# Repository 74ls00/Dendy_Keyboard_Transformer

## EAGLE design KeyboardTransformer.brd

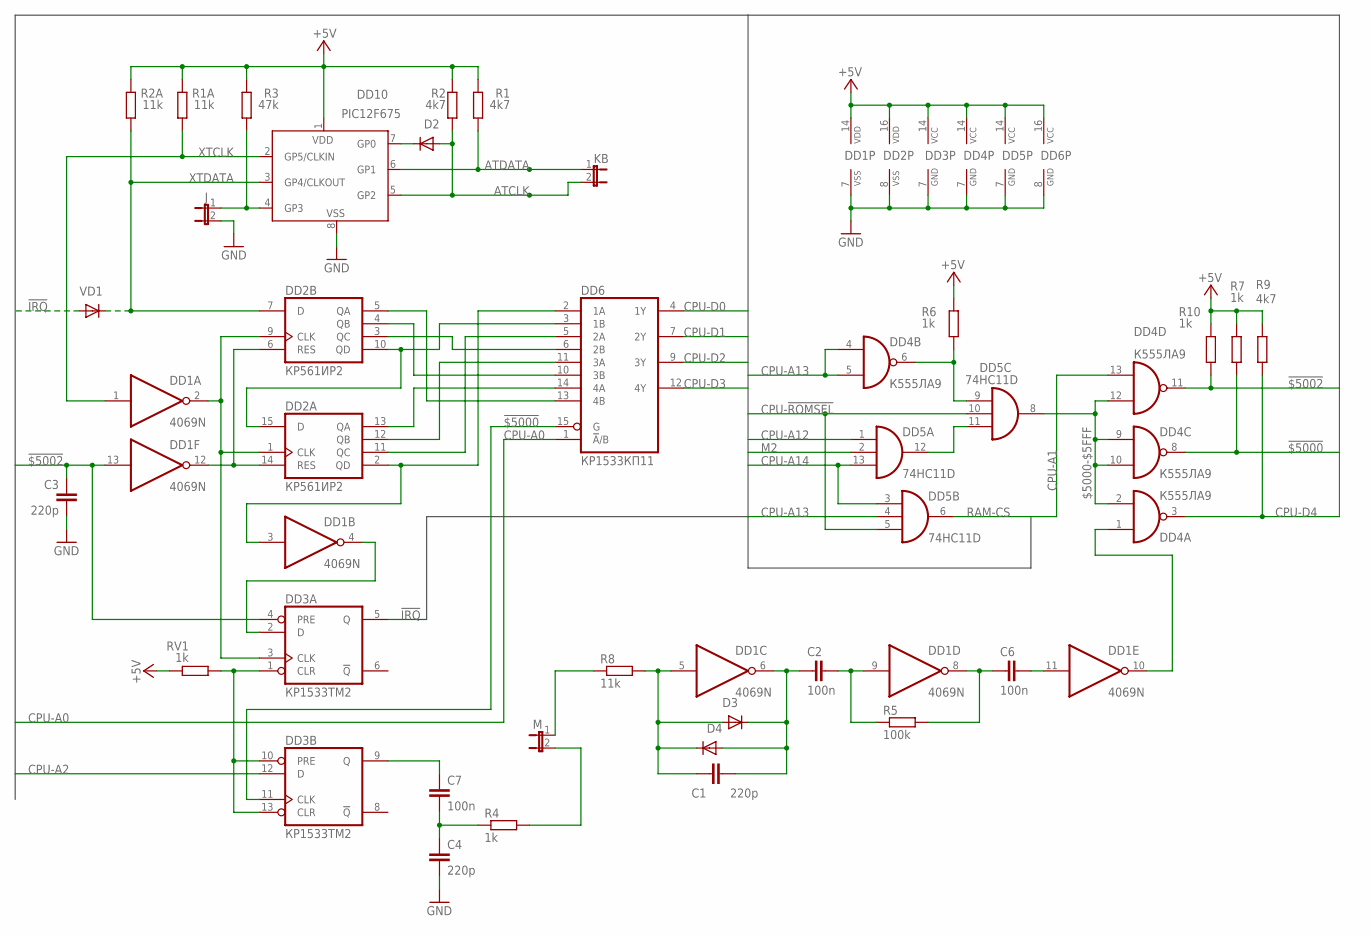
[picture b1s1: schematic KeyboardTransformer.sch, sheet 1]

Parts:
C1, C3, C4: 220p; C0805
C2, C6, C7: 100n; C0805
D2, D3, D4: DIODE-SOD80C; SOD80C
DD1: 4069N; DIL14
DD2: КР561ИР2; DIL16
DD3: КР1533ТМ2; DIL14
DD4: К555ЛА9; DIL14
DD5: 74HC11D; SO14
DD6: КР1533КП11; DIL16
DD10: PIC12F675; SO-08
J: JP1E; JP1
KB: JP1E; JP1
M: JP1E; JP1
R1, R2, R9: 4k7; M0805
R1A, R2A, R8: 11k; M0805
R3: 47k; M0805
R4, R6, R7, R10: 1k; M0805
R5: 100k; M0805
RV1: 1k; M0805
VD1: DIODE-SOD80C; SOD80C

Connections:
!$5000: DD3.11 (CLK), DD4.8 (O), DD6.15 (G), R7.1
!$5002: C3.1, DD1.13 (I), DD3.4 (PRE), DD4.11 (O), R10.1
!IRQ: DD3.5 (Q), VD1.A; also elsewhere on the board
$5000-$5FFF: DD4.2 (I1), DD4.9 (I0), DD4.10 (I1), DD4.12 (I0), DD5.8 (O)
+5V: DD1.14 (VDD), DD2.16 (VDD), DD3.14 (VCC), DD4.14 (VCC), DD5.14 (VCC), DD6.16 (VCC), DD10.1 (VDD), R1.2, R1A.2, R2.2, R2A.2, R3.2, R6.2, R7.2, R9.2, R10.2, RV1.2; also elsewhere on the board
ATCLK: D2.A, DD10.5 (GP2), KB.2, R2.1
ATDATA: DD10.6 (GP1), KB.1, R1.1
CPU-!ROMSEL: DD5.5 (I2), DD5.10 (I1); also elsewhere on the board
CPU-A0: DD6.1 (!A!/B); also elsewhere on the board
CPU-A1: DD4.13 (I1); also elsewhere on the board
CPU-A2: DD3.12 (D); also elsewhere on the board
CPU-A12: DD5.1 (I0); also elsewhere on the board
CPU-A13: DD4.4 (I0), DD4.5 (I1), DD5.4 (I1); also elsewhere on the board
CPU-A14: DD5.3 (I0), DD5.13 (I2); also elsewhere on the board
CPU-D0: DD6.4 (1Y); also elsewhere on the board
CPU-D1: DD6.7 (2Y); also elsewhere on the board
CPU-D2: DD6.9 (3Y); also elsewhere on the board
CPU-D3: DD6.12 (4Y); also elsewhere on the board
CPU-D4: DD4.3 (O), R9.1; also elsewhere on the board
GND: C3.2, C4.2, DD1.7 (VSS), DD2.8 (VSS), DD3.7 (GND), DD4.7 (GND), DD5.7 (GND), DD6.8 (GND), DD10.8 (VSS), J.2; also elsewhere on the board
M2: DD5.2 (I1); also elsewhere on the board
unnamed: DD3.1 (CLR), DD3.10 (PRE), DD3.13 (CLR), RV1.1
unnamed: DD2.10 (QD), DD2.15 (D), DD6.3 (1B)
unnamed: DD1.12 (O), DD2.6 (RES), DD2.14 (RES)
unnamed: DD1.2 (O), DD2.1 (CLK), DD2.9 (CLK), DD3.3 (CLK)
unnamed: DD2.5 (QA), DD6.13 (4B)
unnamed: DD2.4 (QB), DD6.10 (3B)
unnamed: D2.C, DD10.7 (GP0)
unnamed: DD2.3 (QC), DD6.6 (2B)
unnamed: DD2.13 (QA), DD6.14 (4A)
unnamed: DD2.12 (QB), DD6.11 (3A)
unnamed: DD2.11 (QC), DD6.5 (2A)
unnamed: DD10.4 (GP3), J.1, R3.1
unnamed: DD1.3 (I), DD2.2 (QD), DD6.2 (1A)
unnamed: DD1.4 (O), DD3.2 (D)
unnamed: DD5.11 (I2), DD5.12 (O)
unnamed: C7.1, DD3.9 (Q)
unnamed: C4.1, C7.2, R4.1
unnamed: M.1, R8.1
unnamed: DD4.6 (O), DD5.9 (I0), R6.1
unnamed: C1.1, D3.A, D4.C, DD1.5 (I), R8.2
unnamed: C1.2, C2.1, D3.C, D4.A, DD1.6 (O)
unnamed: C6.2, DD1.11 (I)
unnamed: DD1.10 (O), DD4.1 (I0)
unnamed: C2.2, DD1.9 (I), R5.1
unnamed: C6.1, DD1.8 (O), R5.2
unnamed: M.2, R4.2
RAM-CS: DD5.6 (O); also elsewhere on the board
XTCLK: DD1.1 (I), DD10.2 (GP5/CLKIN), R1A.1
XTDATA: DD2.7 (D), DD10.3 (GP4/CLKOUT), R2A.1, VD1.C

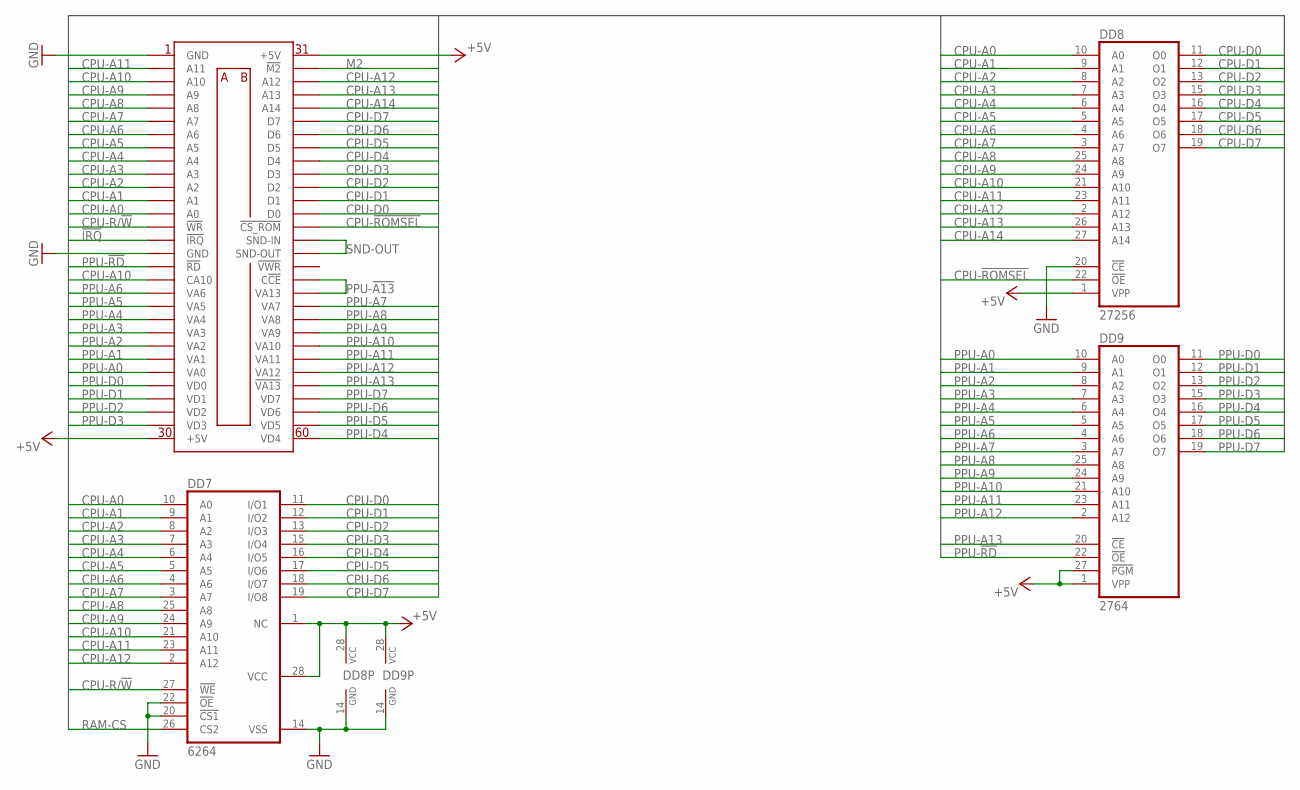
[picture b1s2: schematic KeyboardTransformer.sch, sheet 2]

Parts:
DD7: 6264; DIL28-6
DD8: 27256; DIL28
DD9: 2764; DIL28
U$1: CON60

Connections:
!IRQ: U$1.P$15 (!IRQ); also elsewhere on the board
+5V: DD7.1 (NC), DD7.28 (VCC), DD8.1 (VPP), DD8.28 (VCC), DD9.1 (VPP), DD9.27 (!PGM), DD9.28 (VCC), U$1.P$30 (+5V), U$1.P$31 (+5V); also elsewhere on the board
CPU-!ROMSEL: DD8.22 (!OE), U$1.P$44 (!CS_ROM); also elsewhere on the board
CPU-A0: DD7.10 (A0), DD8.10 (A0), U$1.P$13 (A0); also elsewhere on the board
CPU-A1: DD7.9 (A1), DD8.9 (A1), U$1.P$12 (A1); also elsewhere on the board
CPU-A2: DD7.8 (A2), DD8.8 (A2), U$1.P$11 (A2); also elsewhere on the board
CPU-A3: DD7.7 (A3), DD8.7 (A3), U$1.P$10 (A3)
CPU-A4: DD7.6 (A4), DD8.6 (A4), U$1.P$9 (A4)
CPU-A5: DD7.5 (A5), DD8.5 (A5), U$1.P$8 (A5)
CPU-A6: DD7.4 (A6), DD8.4 (A6), U$1.P$7 (A6)
CPU-A7: DD7.3 (A7), DD8.3 (A7), U$1.P$6 (A7)
CPU-A8: DD7.25 (A8), DD8.25 (A8), U$1.P$5 (A8)
CPU-A9: DD7.24 (A9), DD8.24 (A9), U$1.P$4 (A9)
CPU-A10: DD7.21 (A10), DD8.21 (A10), U$1.P$3 (A10), U$1.P$18 (CA10)
CPU-A11: DD7.23 (A11), DD8.23 (A11), U$1.P$2 (A11)
CPU-A12: DD7.2 (A12), DD8.2 (A12), U$1.P$33 (A12); also elsewhere on the board
CPU-A13: DD8.26 (A13), U$1.P$34 (A13); also elsewhere on the board
CPU-A14: DD8.27 (A14), U$1.P$35 (A14); also elsewhere on the board
CPU-D0: DD7.11 (I/O1), DD8.11 (O0), U$1.P$43 (D0); also elsewhere on the board
CPU-D1: DD7.12 (I/O2), DD8.12 (O1), U$1.P$42 (D1); also elsewhere on the board
CPU-D2: DD7.13 (I/O3), DD8.13 (O2), U$1.P$41 (D2); also elsewhere on the board
CPU-D3: DD7.15 (I/O4), DD8.15 (O3), U$1.P$40 (D3); also elsewhere on the board
CPU-D4: DD7.16 (I/O5), DD8.16 (O4), U$1.P$39 (D4); also elsewhere on the board
CPU-D5: DD7.17 (I/O6), DD8.17 (O5), U$1.P$38 (D5)
CPU-D6: DD7.18 (I/O7), DD8.18 (O6), U$1.P$37 (D6)
CPU-D7: DD7.19 (I/O8), DD8.19 (O7), U$1.P$36 (D7)
CPU-R/!W: DD7.27 (!WE), U$1.P$14 (!WR)
GND: DD7.14 (VSS), DD7.20 (!CS1), DD7.22 (!OE), DD8.14 (GND), DD8.20 (!CE), DD9.14 (GND), U$1.P$1 (GND), U$1.P$16 (GND); also elsewhere on the board
M2: U$1.P$32 (!M2); also elsewhere on the board
PPU-!A13: U$1.P$48 (C!CE), U$1.P$49 (VA13)
PPU-!RD: DD9.22 (!OE), U$1.P$17 (!RD)
PPU-A0: DD9.10 (A0), U$1.P$25 (VA0)
PPU-A1: DD9.9 (A1), U$1.P$24 (VA1)
PPU-A2: DD9.8 (A2), U$1.P$23 (VA2)
PPU-A3: DD9.7 (A3), U$1.P$22 (VA3)
PPU-A4: DD9.6 (A4), U$1.P$21 (VA4)
PPU-A5: DD9.5 (A5), U$1.P$20 (VA5)
PPU-A6: DD9.4 (A6), U$1.P$19 (VA6)
PPU-A7: DD9.3 (A7), U$1.P$50 (VA7)
PPU-A8: DD9.25 (A8), U$1.P$51 (VA8)
PPU-A9: DD9.24 (A9), U$1.P$52 (VA9)
PPU-A10: DD9.21 (A10), U$1.P$53 (VA10)
PPU-A11: DD9.23 (A11), U$1.P$54 (VA11)
PPU-A12: DD9.2 (A12), U$1.P$55 (VA12)
PPU-A13: DD9.20 (!CE), U$1.P$56 (!VA13)
PPU-D0: DD9.11 (O0), U$1.P$26 (VD0)
PPU-D1: DD9.12 (O1), U$1.P$27 (VD1)
PPU-D2: DD9.13 (O2), U$1.P$28 (VD2)
PPU-D3: DD9.15 (O3), U$1.P$29 (VD3)
PPU-D4: DD9.16 (O4), U$1.P$60 (VD4)
PPU-D5: DD9.17 (O5), U$1.P$59 (VD5)
PPU-D6: DD9.18 (O6), U$1.P$58 (VD6)
PPU-D7: DD9.19 (O7), U$1.P$57 (VD7)
RAM-CS: DD7.26 (CS2); also elsewhere on the board
SND-OUT: U$1.P$45 (SND-IN), U$1.P$46 (SND-OUT)

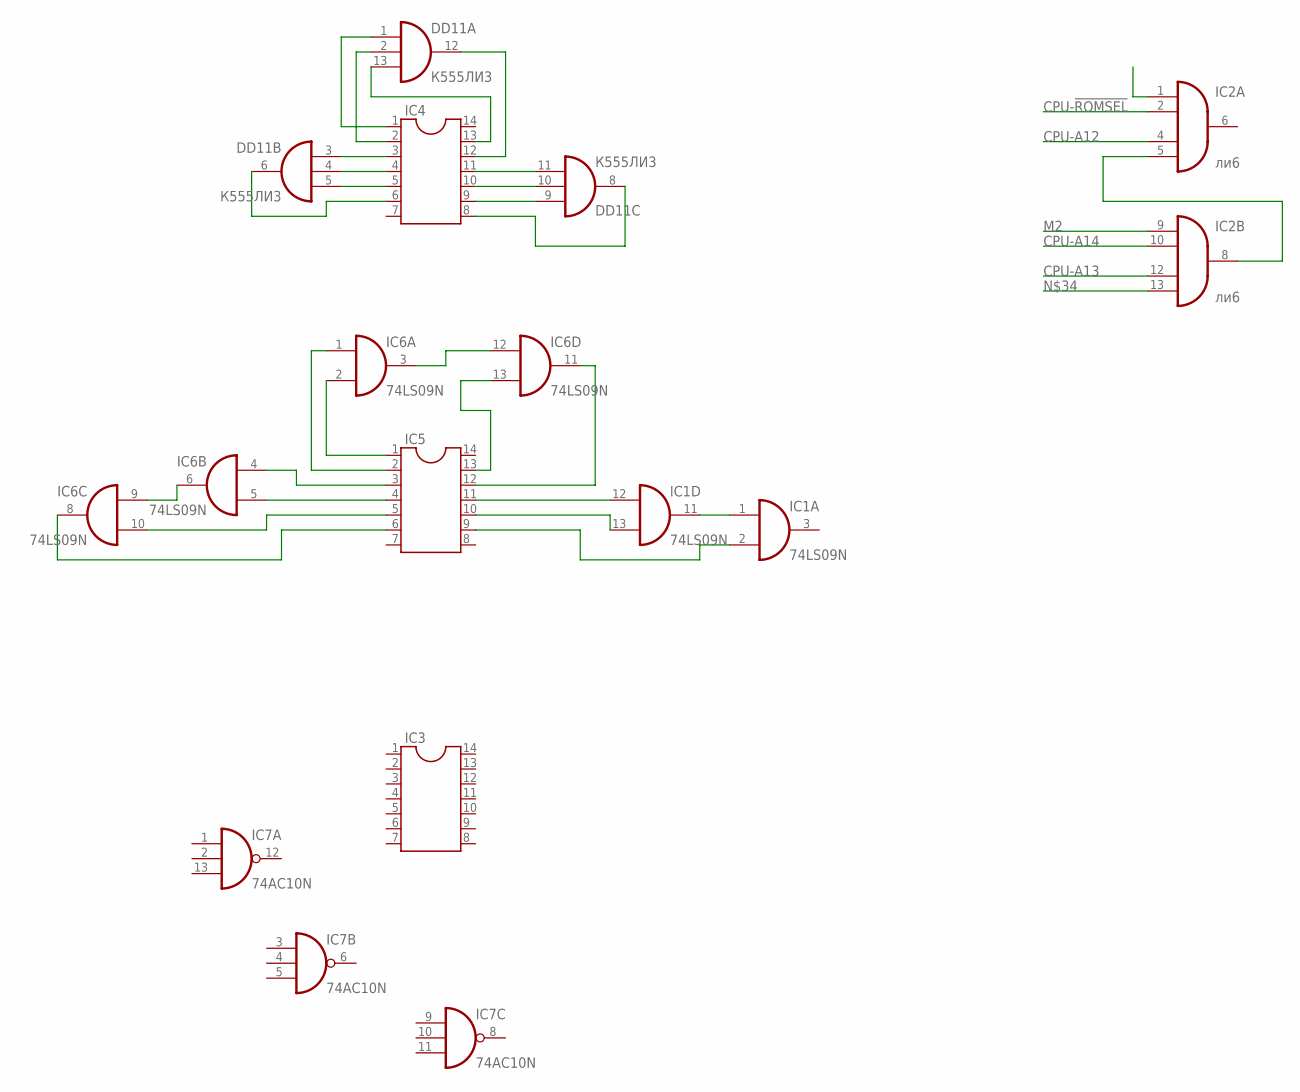
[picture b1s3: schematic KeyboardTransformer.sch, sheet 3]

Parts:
DD11: К555ЛИ3; DIL14
IC1, IC6: 74LS09N; DIL14
IC2: ли6; DIL14
IC3, IC4, IC5: DIL14
IC7: 74AC10N; DIL14

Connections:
CPU-!ROMSEL: IC2.2 (I1); also elsewhere on the board
CPU-A12: IC2.4 (I2); also elsewhere on the board
CPU-A13: IC2.12 (I2); also elsewhere on the board
CPU-A14: IC2.10 (I1); also elsewhere on the board
GND: DD11.7 (GND), IC1.7 (GND), IC2.7 (GND), IC6.7 (GND), IC7.7 (GND); also elsewhere on the board
M2: IC2.9 (I0); also elsewhere on the board
unnamed: IC6.3 (O), IC6.12 (I0)
unnamed: IC5.1, IC6.2 (I1)
unnamed: IC5.2, IC6.1 (I0)
unnamed: IC5.13, IC6.13 (I1)
unnamed: IC5.12, IC6.11 (O)
unnamed: DD11.13 (I2), IC4.13
unnamed: IC2.5 (I3), IC2.8 (O)
unnamed: DD11.12 (O), IC4.12
unnamed: DD11.2 (I1), IC4.2
unnamed: DD11.1 (I0), IC4.1
unnamed: DD11.3 (I0), IC4.3
unnamed: DD11.4 (I1), IC4.4
unnamed: DD11.5 (I2), IC4.5
unnamed: DD11.6 (O), IC4.6
unnamed: DD11.11 (I2), IC4.11
unnamed: DD11.10 (I1), IC4.10
unnamed: DD11.9 (I0), IC4.9
unnamed: DD11.8 (O), IC4.8
unnamed: IC5.3, IC6.4 (I0)
unnamed: IC5.4, IC6.5 (I1)
unnamed: IC6.6 (O), IC6.9 (I0)
unnamed: IC5.5, IC6.10 (I1)
unnamed: IC5.6, IC6.8 (O)
unnamed: IC1.12 (I0), IC5.11
unnamed: IC1.13 (I1), IC5.10
unnamed: IC1.1 (I0), IC1.11 (O)
unnamed: IC1.2 (I1), IC5.9
VCC: DD11.14 (VCC), IC1.14 (VCC), IC2.14 (VCC), IC6.14 (VCC), IC7.14 (VCC)

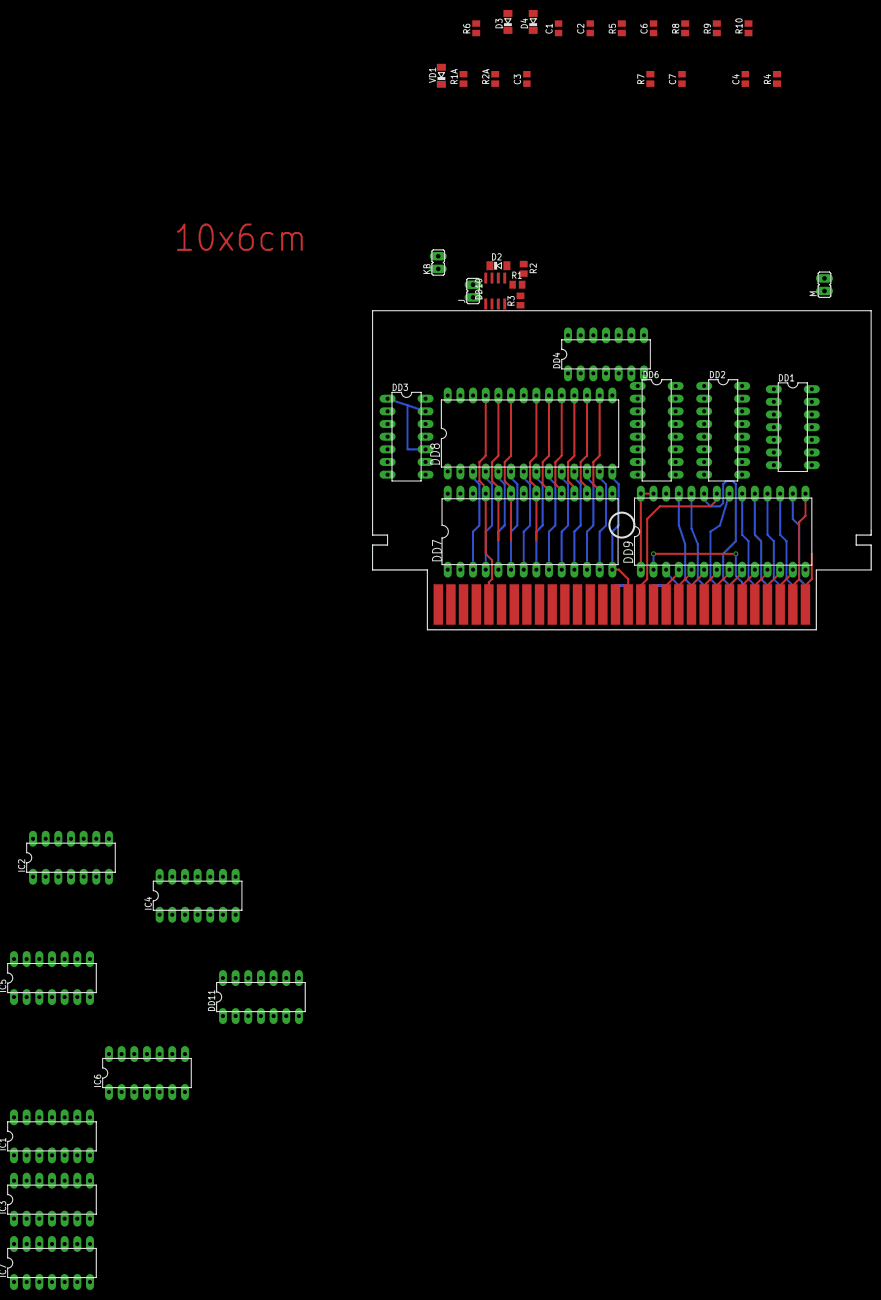
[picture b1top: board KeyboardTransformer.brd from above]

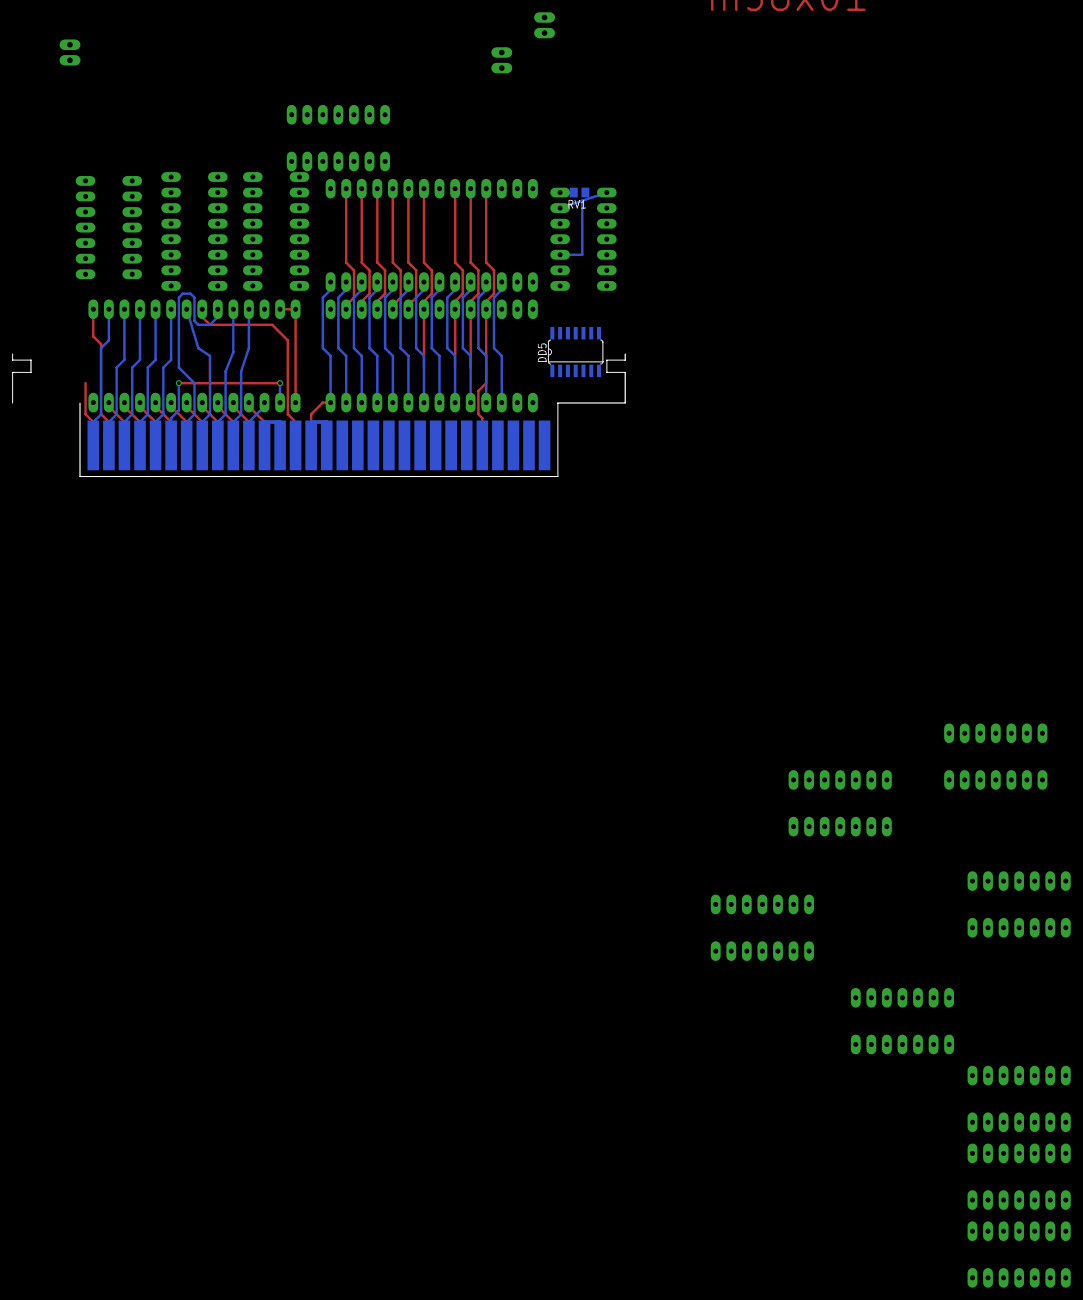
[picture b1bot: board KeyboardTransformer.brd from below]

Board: 2 copper layers, 45 parts (2 on the bottom side), 116 nets.
